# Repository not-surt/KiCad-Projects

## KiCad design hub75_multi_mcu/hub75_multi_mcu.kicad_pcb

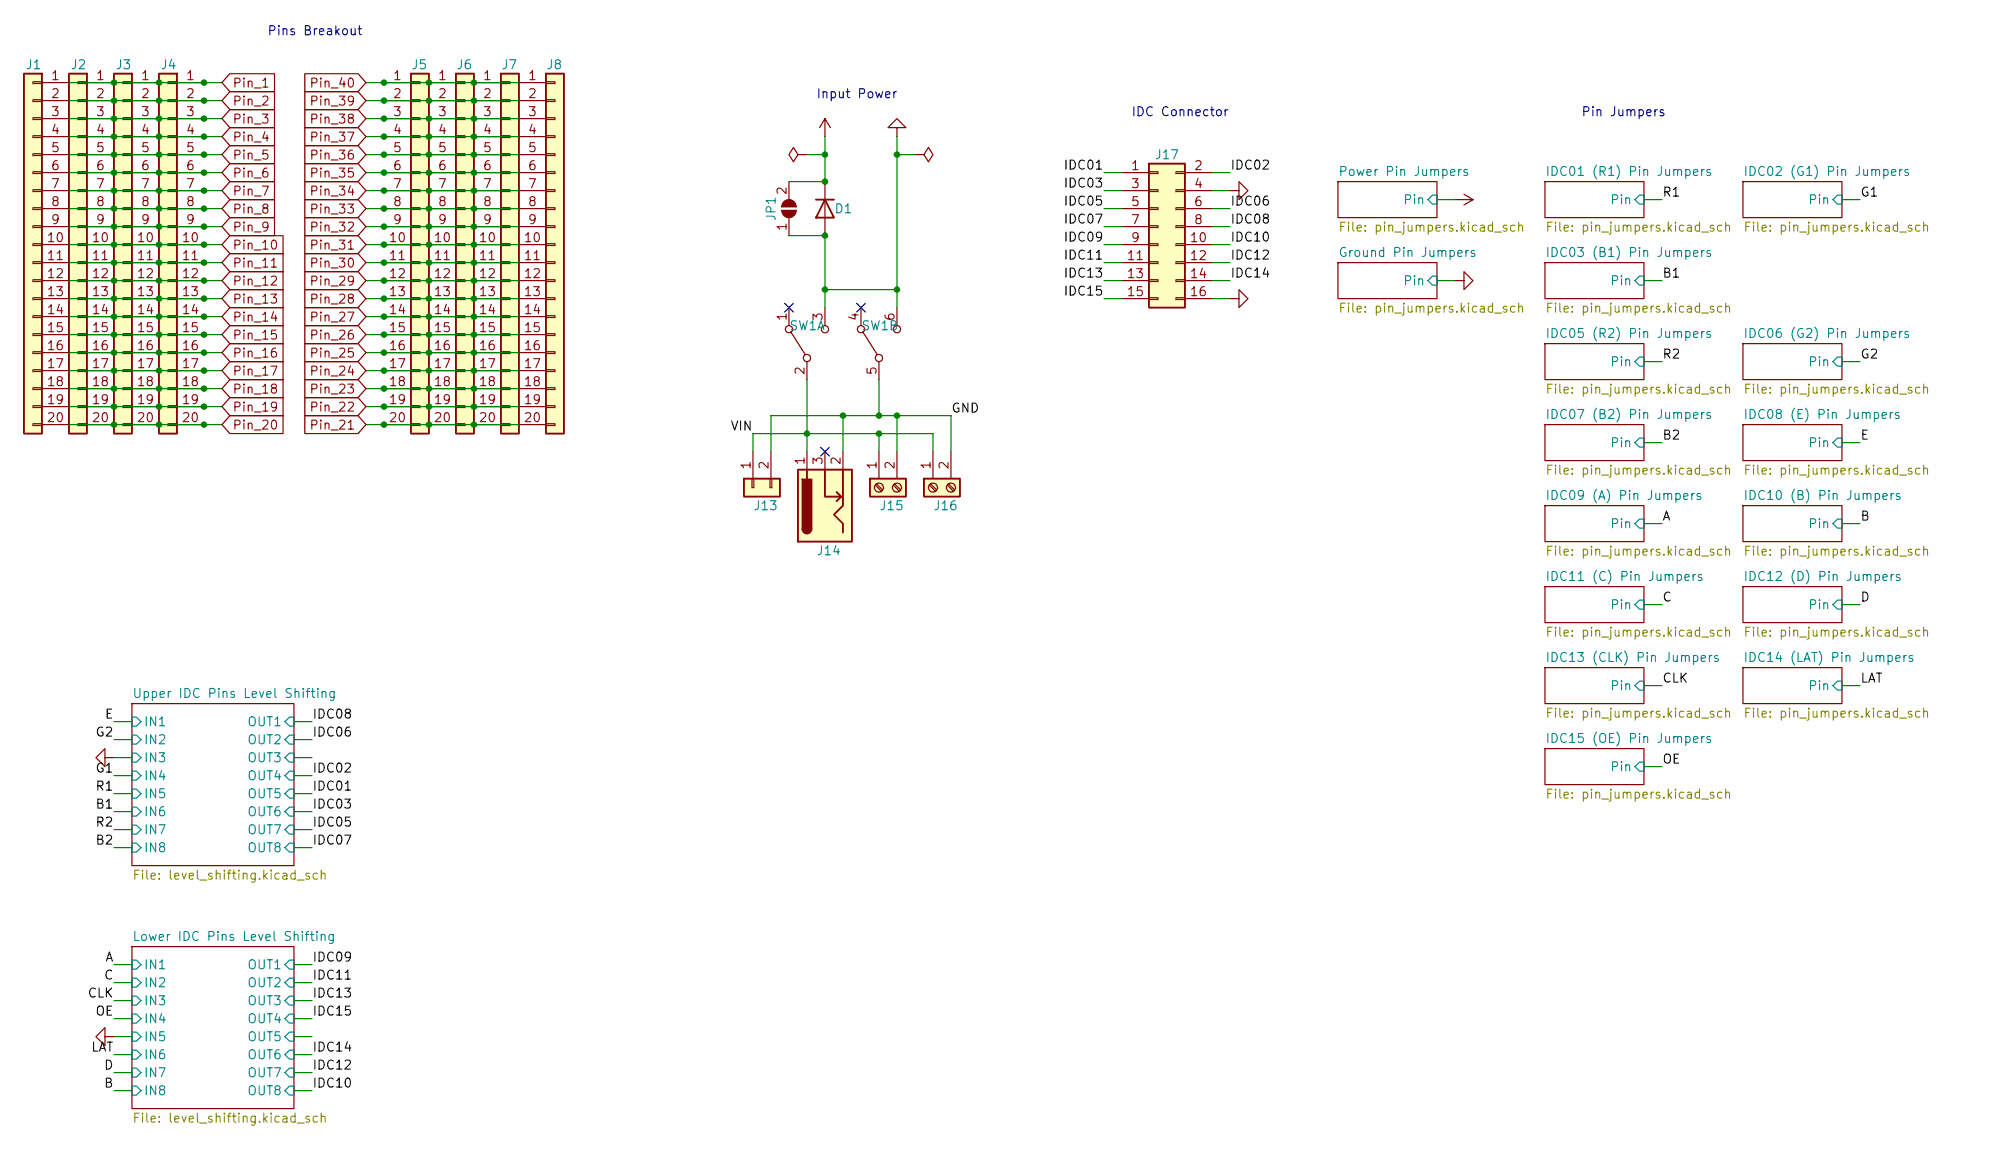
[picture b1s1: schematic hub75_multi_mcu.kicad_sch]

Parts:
D1: D; D_SMA
J1, J2, J3, J4, J5, J6, J7, J8: Conn_01x20; PinHeader_1x20_P2.54mm_Vertical_No_Silk
J13: Conn_01x02; PinHeader_1x02_P2.54mm_Vertical
J14: Barrel_Jack; BarrelJack_Horizontal
J15: Screw_Terminal_01x02; TerminalBlock_bornier-2_P5.08mm
J16: Screw_Terminal_01x02; Barrier_Block
J17: Conn_02x08_Odd_Even; IDC-Header_2x08_P2.54mm_Vertical
JP1: SolderJumper_2_Open; SolderJumper-mini-2
SW1: SW_DPDT; SW_CuK_JS202011CQN_DPDT_Straight

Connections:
/IDC01: J17.1; also elsewhere on the board
/IDC02: J17.2; also elsewhere on the board
/IDC03: J17.3; also elsewhere on the board
/IDC05: J17.5; also elsewhere on the board
/IDC06: J17.6; also elsewhere on the board
/IDC07: J17.7; also elsewhere on the board
/IDC08: J17.8; also elsewhere on the board
/IDC09: J17.9; also elsewhere on the board
/IDC10: J17.10; also elsewhere on the board
/IDC11: J17.11; also elsewhere on the board
/IDC12: J17.12; also elsewhere on the board
/IDC13: J17.13; also elsewhere on the board
/IDC14: J17.14; also elsewhere on the board
/IDC15: J17.15; also elsewhere on the board
/VIN: J13.1, J14.1, J15.1, J16.1, SW1.2 (B)
GND: D1.2 (A), J13.2, J14.2, J15.2, J16.2, J17.4, J17.16, JP1.1 (A), SW1.3 (C), SW1.5 (B), SW1.6 (C); also elsewhere on the board
Pin_1: J1.1, J2.1, J3.1, J4.1; also elsewhere on the board
Pin_2: J1.2, J2.2, J3.2, J4.2; also elsewhere on the board
Pin_3: J1.3, J2.3, J3.3, J4.3; also elsewhere on the board
Pin_4: J1.4, J2.4, J3.4, J4.4; also elsewhere on the board
Pin_5: J1.5, J2.5, J3.5, J4.5; also elsewhere on the board
Pin_6: J1.6, J2.6, J3.6, J4.6; also elsewhere on the board
Pin_7: J1.7, J2.7, J3.7, J4.7; also elsewhere on the board
Pin_8: J1.8, J2.8, J3.8, J4.8; also elsewhere on the board
Pin_9: J1.9, J2.9, J3.9, J4.9; also elsewhere on the board
Pin_10: J1.10, J2.10, J3.10, J4.10; also elsewhere on the board
Pin_11: J1.11, J2.11, J3.11, J4.11; also elsewhere on the board
Pin_12: J1.12, J2.12, J3.12, J4.12; also elsewhere on the board
Pin_13: J1.13, J2.13, J3.13, J4.13; also elsewhere on the board
Pin_14: J1.14, J2.14, J3.14, J4.14; also elsewhere on the board
Pin_15: J1.15, J2.15, J3.15, J4.15; also elsewhere on the board
Pin_16: J1.16, J2.16, J3.16, J4.16; also elsewhere on the board
Pin_17: J1.17, J2.17, J3.17, J4.17; also elsewhere on the board
Pin_18: J1.18, J2.18, J3.18, J4.18; also elsewhere on the board
Pin_19: J1.19, J2.19, J3.19, J4.19; also elsewhere on the board
Pin_20: J1.20, J2.20, J3.20, J4.20; also elsewhere on the board
Pin_21: J5.20, J6.20, J7.20, J8.20; also elsewhere on the board
Pin_22: J5.19, J6.19, J7.19, J8.19; also elsewhere on the board
Pin_23: J5.18, J6.18, J7.18, J8.18; also elsewhere on the board
Pin_24: J5.17, J6.17, J7.17, J8.17; also elsewhere on the board
Pin_25: J5.16, J6.16, J7.16, J8.16; also elsewhere on the board
Pin_26: J5.15, J6.15, J7.15, J8.15; also elsewhere on the board
Pin_27: J5.14, J6.14, J7.14, J8.14; also elsewhere on the board
Pin_28: J5.13, J6.13, J7.13, J8.13; also elsewhere on the board
Pin_29: J5.12, J6.12, J7.12, J8.12; also elsewhere on the board
Pin_30: J5.11, J6.11, J7.11, J8.11; also elsewhere on the board
Pin_31: J5.10, J6.10, J7.10, J8.10; also elsewhere on the board
Pin_32: J5.9, J6.9, J7.9, J8.9; also elsewhere on the board
Pin_33: J5.8, J6.8, J7.8, J8.8; also elsewhere on the board
Pin_34: J5.7, J6.7, J7.7, J8.7; also elsewhere on the board
Pin_35: J5.6, J6.6, J7.6, J8.6; also elsewhere on the board
Pin_36: J5.5, J6.5, J7.5, J8.5; also elsewhere on the board
Pin_37: J5.4, J6.4, J7.4, J8.4; also elsewhere on the board
Pin_38: J5.3, J6.3, J7.3, J8.3; also elsewhere on the board
Pin_39: J5.2, J6.2, J7.2, J8.2; also elsewhere on the board
Pin_40: J5.1, J6.1, J7.1, J8.1; also elsewhere on the board
VCC: D1.1 (K), JP1.2 (B); also elsewhere on the board

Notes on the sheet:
Pins Breakout
IDC Connector
Input Power
Pin Jumpers

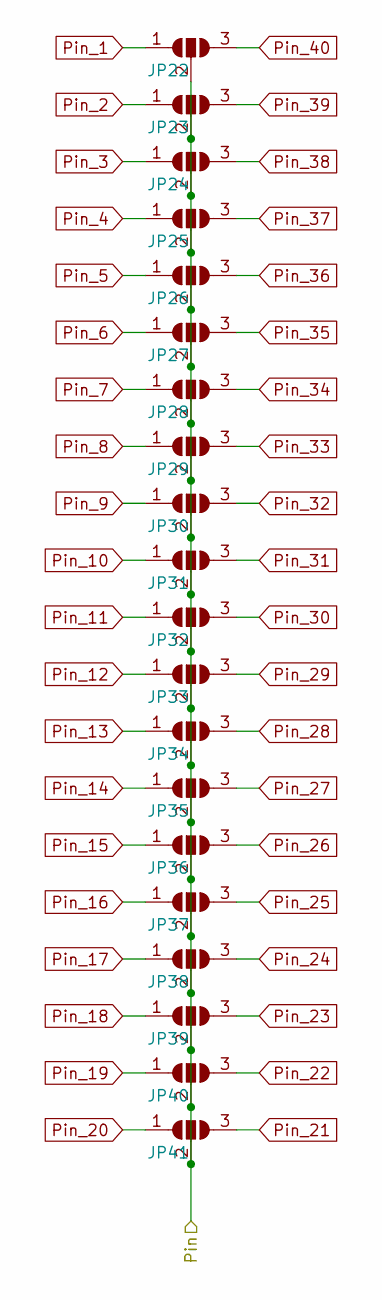
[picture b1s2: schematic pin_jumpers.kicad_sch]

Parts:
JP22, JP23, JP24, JP25, JP26, JP27, JP28, JP29, JP30, JP31, JP32, JP33, JP34, JP35, JP36, JP37, JP38, JP39, JP40, JP41: SolderJumper_3_Open; SolderJumper-mini-3

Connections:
Pin_1: JP22.1 (A); also elsewhere on the board
Pin_2: JP23.1 (A); also elsewhere on the board
Pin_3: JP24.1 (A); also elsewhere on the board
Pin_4: JP25.1 (A); also elsewhere on the board
Pin_5: JP26.1 (A); also elsewhere on the board
Pin_6: JP27.1 (A); also elsewhere on the board
Pin_7: JP28.1 (A); also elsewhere on the board
Pin_8: JP29.1 (A); also elsewhere on the board
Pin_9: JP30.1 (A); also elsewhere on the board
Pin_10: JP31.1 (A); also elsewhere on the board
Pin_11: JP32.1 (A); also elsewhere on the board
Pin_12: JP33.1 (A); also elsewhere on the board
Pin_13: JP34.1 (A); also elsewhere on the board
Pin_14: JP35.1 (A); also elsewhere on the board
Pin_15: JP36.1 (A); also elsewhere on the board
Pin_16: JP37.1 (A); also elsewhere on the board
Pin_17: JP38.1 (A); also elsewhere on the board
Pin_18: JP39.1 (A); also elsewhere on the board
Pin_19: JP40.1 (A); also elsewhere on the board
Pin_20: JP41.1 (A); also elsewhere on the board
Pin_21: JP41.3 (B); also elsewhere on the board
Pin_22: JP40.3 (B); also elsewhere on the board
Pin_23: JP39.3 (B); also elsewhere on the board
Pin_24: JP38.3 (B); also elsewhere on the board
Pin_25: JP37.3 (B); also elsewhere on the board
Pin_26: JP36.3 (B); also elsewhere on the board
Pin_27: JP35.3 (B); also elsewhere on the board
Pin_28: JP34.3 (B); also elsewhere on the board
Pin_29: JP33.3 (B); also elsewhere on the board
Pin_30: JP32.3 (B); also elsewhere on the board
Pin_31: JP31.3 (B); also elsewhere on the board
Pin_32: JP30.3 (B); also elsewhere on the board
Pin_33: JP29.3 (B); also elsewhere on the board
Pin_34: JP28.3 (B); also elsewhere on the board
Pin_35: JP27.3 (B); also elsewhere on the board
Pin_36: JP26.3 (B); also elsewhere on the board
Pin_37: JP25.3 (B); also elsewhere on the board
Pin_38: JP24.3 (B); also elsewhere on the board
Pin_39: JP23.3 (B); also elsewhere on the board
Pin_40: JP22.3 (B); also elsewhere on the board
VCC: JP22.2 (C), JP23.2 (C), JP24.2 (C), JP25.2 (C), JP26.2 (C), JP27.2 (C), JP28.2 (C), JP29.2 (C), JP30.2 (C), JP31.2 (C), JP32.2 (C), JP33.2 (C), JP34.2 (C), JP35.2 (C), JP36.2 (C), JP37.2 (C), JP38.2 (C), JP39.2 (C), JP40.2 (C), JP41.2 (C); also elsewhere on the board

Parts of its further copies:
JP2, JP3, JP4, JP5, JP6, JP7, JP8, JP9, JP10, JP11, JP12, JP13, JP14, JP15, JP16, JP17, JP18, JP19, JP20, JP21, JP42, JP43, JP44, JP45, JP46, JP47, JP48, JP49, JP50, JP51, JP52, JP53, JP54, JP55, JP56, JP57, JP58, JP59, JP60, JP61, JP62, JP63, JP64, JP65, JP66, JP67, JP68, JP69, JP70, JP71, JP72, JP73, JP74, JP75, JP76, JP77, JP78, JP79, JP80, JP81, JP82, JP83, JP84, JP85, JP86, JP87, JP88, JP89, JP90, JP91, JP92, JP93, JP94, JP95, JP96, JP97, JP98, JP99, JP100, JP101, JP102, JP103, JP104, JP105, JP106, JP107, JP108, JP109, JP110, JP111, JP112, JP113, JP114, JP115, JP116, JP117, JP118, JP119, JP120, JP121, JP122, JP123, JP124, JP125, JP126, JP127, JP128, JP129, JP130, JP131, JP132, JP133, JP134, JP135, JP136, JP137, JP138, JP139, JP140, JP141, JP142, JP143, JP144, JP145, JP146, JP147, JP148, JP149, JP150, JP151, JP152, JP153, JP154, JP155, JP156, JP157, JP158, JP159, JP160, JP161, JP162, JP163, JP164, JP165, JP166, JP167, JP168, JP169, JP170, JP171, JP172, JP173, JP174, JP175, JP176, JP177, JP178, JP179, JP180, JP181, JP182, JP183, JP184, JP185, JP186, JP187, JP188, JP189, JP190, JP191, JP192, JP193, JP194, JP195, JP196, JP197, JP198, JP199, JP200, JP201, JP202, JP203, JP204, JP205, JP206, JP207, JP208, JP209, JP210, JP211, JP212, JP213, JP214, JP215, JP216, JP217, JP218, JP219, JP220, JP221, JP222, JP223, JP224, JP225, JP226, JP227, JP228, JP229, JP230, JP231, JP232, JP233, JP234, JP235, JP236, JP237, JP238, JP239, JP240, JP241, JP242, JP243, JP244, JP245, JP246, JP247, JP248, JP249, JP250, JP251, JP252, JP253, JP254, JP255, JP256, JP257, JP258, JP259, JP260, JP261, JP262, JP263, JP264, JP265, JP266, JP267, JP268, JP269, JP270, JP271, JP272, JP273, JP274, JP275, JP276, JP277, JP278, JP279, JP280, JP281, JP282, JP283, JP284, JP285, JP286, JP287, JP288, JP289, JP290, JP291, JP292, JP293, JP294, JP295, JP296, JP297, JP298, JP299, JP300, JP301, JP302, JP303, JP304, JP305, JP306, JP307, JP308, JP309, JP310, JP311, JP312, JP313, JP314, JP315, JP316, JP317, JP318, JP319, JP320, JP321: SolderJumper_3_Open; SolderJumper-mini-3

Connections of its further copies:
/A: JP182.2 (C), JP183.2 (C), JP184.2 (C), JP185.2 (C), JP186.2 (C), JP187.2 (C), JP188.2 (C), JP189.2 (C), JP190.2 (C), JP191.2 (C), JP192.2 (C), JP193.2 (C), JP194.2 (C), JP195.2 (C), JP196.2 (C), JP197.2 (C), JP198.2 (C), JP199.2 (C), JP200.2 (C), JP201.2 (C); also elsewhere on the board
/B: JP202.2 (C), JP203.2 (C), JP204.2 (C), JP205.2 (C), JP206.2 (C), JP207.2 (C), JP208.2 (C), JP209.2 (C), JP210.2 (C), JP211.2 (C), JP212.2 (C), JP213.2 (C), JP214.2 (C), JP215.2 (C), JP216.2 (C), JP217.2 (C), JP218.2 (C), JP219.2 (C), JP220.2 (C), JP221.2 (C); also elsewhere on the board
/B1: JP82.2 (C), JP83.2 (C), JP84.2 (C), JP85.2 (C), JP86.2 (C), JP87.2 (C), JP88.2 (C), JP89.2 (C), JP90.2 (C), JP91.2 (C), JP92.2 (C), JP93.2 (C), JP94.2 (C), JP95.2 (C), JP96.2 (C), JP97.2 (C), JP98.2 (C), JP99.2 (C), JP100.2 (C), JP101.2 (C); also elsewhere on the board
/B2: JP142.2 (C), JP143.2 (C), JP144.2 (C), JP145.2 (C), JP146.2 (C), JP147.2 (C), JP148.2 (C), JP149.2 (C), JP150.2 (C), JP151.2 (C), JP152.2 (C), JP153.2 (C), JP154.2 (C), JP155.2 (C), JP156.2 (C), JP157.2 (C), JP158.2 (C), JP159.2 (C), JP160.2 (C), JP161.2 (C); also elsewhere on the board
/C: JP222.2 (C), JP223.2 (C), JP224.2 (C), JP225.2 (C), JP226.2 (C), JP227.2 (C), JP228.2 (C), JP229.2 (C), JP230.2 (C), JP231.2 (C), JP232.2 (C), JP233.2 (C), JP234.2 (C), JP235.2 (C), JP236.2 (C), JP237.2 (C), JP238.2 (C), JP239.2 (C), JP240.2 (C), JP241.2 (C); also elsewhere on the board
/CLK: JP262.2 (C), JP263.2 (C), JP264.2 (C), JP265.2 (C), JP266.2 (C), JP267.2 (C), JP268.2 (C), JP269.2 (C), JP270.2 (C), JP271.2 (C), JP272.2 (C), JP273.2 (C), JP274.2 (C), JP275.2 (C), JP276.2 (C), JP277.2 (C), JP278.2 (C), JP279.2 (C), JP280.2 (C), JP281.2 (C); also elsewhere on the board
/D: JP242.2 (C), JP243.2 (C), JP244.2 (C), JP245.2 (C), JP246.2 (C), JP247.2 (C), JP248.2 (C), JP249.2 (C), JP250.2 (C), JP251.2 (C), JP252.2 (C), JP253.2 (C), JP254.2 (C), JP255.2 (C), JP256.2 (C), JP257.2 (C), JP258.2 (C), JP259.2 (C), JP260.2 (C), JP261.2 (C); also elsewhere on the board
/E: JP162.2 (C), JP163.2 (C), JP164.2 (C), JP165.2 (C), JP166.2 (C), JP167.2 (C), JP168.2 (C), JP169.2 (C), JP170.2 (C), JP171.2 (C), JP172.2 (C), JP173.2 (C), JP174.2 (C), JP175.2 (C), JP176.2 (C), JP177.2 (C), JP178.2 (C), JP179.2 (C), JP180.2 (C), JP181.2 (C); also elsewhere on the board
/G1: JP62.2 (C), JP63.2 (C), JP64.2 (C), JP65.2 (C), JP66.2 (C), JP67.2 (C), JP68.2 (C), JP69.2 (C), JP70.2 (C), JP71.2 (C), JP72.2 (C), JP73.2 (C), JP74.2 (C), JP75.2 (C), JP76.2 (C), JP77.2 (C), JP78.2 (C), JP79.2 (C), JP80.2 (C), JP81.2 (C); also elsewhere on the board
/G2: JP122.2 (C), JP123.2 (C), JP124.2 (C), JP125.2 (C), JP126.2 (C), JP127.2 (C), JP128.2 (C), JP129.2 (C), JP130.2 (C), JP131.2 (C), JP132.2 (C), JP133.2 (C), JP134.2 (C), JP135.2 (C), JP136.2 (C), JP137.2 (C), JP138.2 (C), JP139.2 (C), JP140.2 (C), JP141.2 (C); also elsewhere on the board
/LAT: JP282.2 (C), JP283.2 (C), JP284.2 (C), JP285.2 (C), JP286.2 (C), JP287.2 (C), JP288.2 (C), JP289.2 (C), JP290.2 (C), JP291.2 (C), JP292.2 (C), JP293.2 (C), JP294.2 (C), JP295.2 (C), JP296.2 (C), JP297.2 (C), JP298.2 (C), JP299.2 (C), JP300.2 (C), JP301.2 (C); also elsewhere on the board
/OE: JP302.2 (C), JP303.2 (C), JP304.2 (C), JP305.2 (C), JP306.2 (C), JP307.2 (C), JP308.2 (C), JP309.2 (C), JP310.2 (C), JP311.2 (C), JP312.2 (C), JP313.2 (C), JP314.2 (C), JP315.2 (C), JP316.2 (C), JP317.2 (C), JP318.2 (C), JP319.2 (C), JP320.2 (C), JP321.2 (C); also elsewhere on the board
/R1: JP42.2 (C), JP43.2 (C), JP44.2 (C), JP45.2 (C), JP46.2 (C), JP47.2 (C), JP48.2 (C), JP49.2 (C), JP50.2 (C), JP51.2 (C), JP52.2 (C), JP53.2 (C), JP54.2 (C), JP55.2 (C), JP56.2 (C), JP57.2 (C), JP58.2 (C), JP59.2 (C), JP60.2 (C), JP61.2 (C); also elsewhere on the board
/R2: JP102.2 (C), JP103.2 (C), JP104.2 (C), JP105.2 (C), JP106.2 (C), JP107.2 (C), JP108.2 (C), JP109.2 (C), JP110.2 (C), JP111.2 (C), JP112.2 (C), JP113.2 (C), JP114.2 (C), JP115.2 (C), JP116.2 (C), JP117.2 (C), JP118.2 (C), JP119.2 (C), JP120.2 (C), JP121.2 (C); also elsewhere on the board
GND: JP2.2 (C), JP3.2 (C), JP4.2 (C), JP5.2 (C), JP6.2 (C), JP7.2 (C), JP8.2 (C), JP9.2 (C), JP10.2 (C), JP11.2 (C), JP12.2 (C), JP13.2 (C), JP14.2 (C), JP15.2 (C), JP16.2 (C), JP17.2 (C), JP18.2 (C), JP19.2 (C), JP20.2 (C), JP21.2 (C); also elsewhere on the board
Pin_1: JP2.1 (A), JP42.1 (A), JP62.1 (A), JP82.1 (A), JP102.1 (A), JP122.1 (A), JP142.1 (A), JP162.1 (A), JP182.1 (A), JP202.1 (A), JP222.1 (A), JP242.1 (A), JP262.1 (A), JP282.1 (A), JP302.1 (A); also elsewhere on the board
Pin_2: JP3.1 (A), JP43.1 (A), JP63.1 (A), JP83.1 (A), JP103.1 (A), JP123.1 (A), JP143.1 (A), JP163.1 (A), JP183.1 (A), JP203.1 (A), JP223.1 (A), JP243.1 (A), JP263.1 (A), JP283.1 (A), JP303.1 (A); also elsewhere on the board
Pin_3: JP4.1 (A), JP44.1 (A), JP64.1 (A), JP84.1 (A), JP104.1 (A), JP124.1 (A), JP144.1 (A), JP164.1 (A), JP184.1 (A), JP204.1 (A), JP224.1 (A), JP244.1 (A), JP264.1 (A), JP284.1 (A), JP304.1 (A); also elsewhere on the board
Pin_4: JP5.1 (A), JP45.1 (A), JP65.1 (A), JP85.1 (A), JP105.1 (A), JP125.1 (A), JP145.1 (A), JP165.1 (A), JP185.1 (A), JP205.1 (A), JP225.1 (A), JP245.1 (A), JP265.1 (A), JP285.1 (A), JP305.1 (A); also elsewhere on the board
Pin_5: JP6.1 (A), JP46.1 (A), JP66.1 (A), JP86.1 (A), JP106.1 (A), JP126.1 (A), JP146.1 (A), JP166.1 (A), JP186.1 (A), JP206.1 (A), JP226.1 (A), JP246.1 (A), JP266.1 (A), JP286.1 (A), JP306.1 (A); also elsewhere on the board
Pin_6: JP7.1 (A), JP47.1 (A), JP67.1 (A), JP87.1 (A), JP107.1 (A), JP127.1 (A), JP147.1 (A), JP167.1 (A), JP187.1 (A), JP207.1 (A), JP227.1 (A), JP247.1 (A), JP267.1 (A), JP287.1 (A), JP307.1 (A); also elsewhere on the board
Pin_7: JP8.1 (A), JP48.1 (A), JP68.1 (A), JP88.1 (A), JP108.1 (A), JP128.1 (A), JP148.1 (A), JP168.1 (A), JP188.1 (A), JP208.1 (A), JP228.1 (A), JP248.1 (A), JP268.1 (A), JP288.1 (A), JP308.1 (A); also elsewhere on the board
Pin_8: JP9.1 (A), JP49.1 (A), JP69.1 (A), JP89.1 (A), JP109.1 (A), JP129.1 (A), JP149.1 (A), JP169.1 (A), JP189.1 (A), JP209.1 (A), JP229.1 (A), JP249.1 (A), JP269.1 (A), JP289.1 (A), JP309.1 (A); also elsewhere on the board
Pin_9: JP10.1 (A), JP50.1 (A), JP70.1 (A), JP90.1 (A), JP110.1 (A), JP130.1 (A), JP150.1 (A), JP170.1 (A), JP190.1 (A), JP210.1 (A), JP230.1 (A), JP250.1 (A), JP270.1 (A), JP290.1 (A), JP310.1 (A); also elsewhere on the board
Pin_10: JP11.1 (A), JP51.1 (A), JP71.1 (A), JP91.1 (A), JP111.1 (A), JP131.1 (A), JP151.1 (A), JP171.1 (A), JP191.1 (A), JP211.1 (A), JP231.1 (A), JP251.1 (A), JP271.1 (A), JP291.1 (A), JP311.1 (A); also elsewhere on the board
Pin_11: JP12.1 (A), JP52.1 (A), JP72.1 (A), JP92.1 (A), JP112.1 (A), JP132.1 (A), JP152.1 (A), JP172.1 (A), JP192.1 (A), JP212.1 (A), JP232.1 (A), JP252.1 (A), JP272.1 (A), JP292.1 (A), JP312.1 (A); also elsewhere on the board
Pin_12: JP13.1 (A), JP53.1 (A), JP73.1 (A), JP93.1 (A), JP113.1 (A), JP133.1 (A), JP153.1 (A), JP173.1 (A), JP193.1 (A), JP213.1 (A), JP233.1 (A), JP253.1 (A), JP273.1 (A), JP293.1 (A), JP313.1 (A); also elsewhere on the board
Pin_13: JP14.1 (A), JP54.1 (A), JP74.1 (A), JP94.1 (A), JP114.1 (A), JP134.1 (A), JP154.1 (A), JP174.1 (A), JP194.1 (A), JP214.1 (A), JP234.1 (A), JP254.1 (A), JP274.1 (A), JP294.1 (A), JP314.1 (A); also elsewhere on the board
Pin_14: JP15.1 (A), JP55.1 (A), JP75.1 (A), JP95.1 (A), JP115.1 (A), JP135.1 (A), JP155.1 (A), JP175.1 (A), JP195.1 (A), JP215.1 (A), JP235.1 (A), JP255.1 (A), JP275.1 (A), JP295.1 (A), JP315.1 (A); also elsewhere on the board
Pin_15: JP16.1 (A), JP56.1 (A), JP76.1 (A), JP96.1 (A), JP116.1 (A), JP136.1 (A), JP156.1 (A), JP176.1 (A), JP196.1 (A), JP216.1 (A), JP236.1 (A), JP256.1 (A), JP276.1 (A), JP296.1 (A), JP316.1 (A); also elsewhere on the board
Pin_16: JP17.1 (A), JP57.1 (A), JP77.1 (A), JP97.1 (A), JP117.1 (A), JP137.1 (A), JP157.1 (A), JP177.1 (A), JP197.1 (A), JP217.1 (A), JP237.1 (A), JP257.1 (A), JP277.1 (A), JP297.1 (A), JP317.1 (A); also elsewhere on the board
Pin_17: JP18.1 (A), JP58.1 (A), JP78.1 (A), JP98.1 (A), JP118.1 (A), JP138.1 (A), JP158.1 (A), JP178.1 (A), JP198.1 (A), JP218.1 (A), JP238.1 (A), JP258.1 (A), JP278.1 (A), JP298.1 (A), JP318.1 (A); also elsewhere on the board
Pin_18: JP19.1 (A), JP59.1 (A), JP79.1 (A), JP99.1 (A), JP119.1 (A), JP139.1 (A), JP159.1 (A), JP179.1 (A), JP199.1 (A), JP219.1 (A), JP239.1 (A), JP259.1 (A), JP279.1 (A), JP299.1 (A), JP319.1 (A); also elsewhere on the board
Pin_19: JP20.1 (A), JP60.1 (A), JP80.1 (A), JP100.1 (A), JP120.1 (A), JP140.1 (A), JP160.1 (A), JP180.1 (A), JP200.1 (A), JP220.1 (A), JP240.1 (A), JP260.1 (A), JP280.1 (A), JP300.1 (A), JP320.1 (A); also elsewhere on the board
Pin_20: JP21.1 (A), JP61.1 (A), JP81.1 (A), JP101.1 (A), JP121.1 (A), JP141.1 (A), JP161.1 (A), JP181.1 (A), JP201.1 (A), JP221.1 (A), JP241.1 (A), JP261.1 (A), JP281.1 (A), JP301.1 (A), JP321.1 (A); also elsewhere on the board
Pin_21: JP21.3 (B), JP61.3 (B), JP81.3 (B), JP101.3 (B), JP121.3 (B), JP141.3 (B), JP161.3 (B), JP181.3 (B), JP201.3 (B), JP221.3 (B), JP241.3 (B), JP261.3 (B), JP281.3 (B), JP301.3 (B), JP321.3 (B); also elsewhere on the board
Pin_22: JP20.3 (B), JP60.3 (B), JP80.3 (B), JP100.3 (B), JP120.3 (B), JP140.3 (B), JP160.3 (B), JP180.3 (B), JP200.3 (B), JP220.3 (B), JP240.3 (B), JP260.3 (B), JP280.3 (B), JP300.3 (B), JP320.3 (B); also elsewhere on the board
Pin_23: JP19.3 (B), JP59.3 (B), JP79.3 (B), JP99.3 (B), JP119.3 (B), JP139.3 (B), JP159.3 (B), JP179.3 (B), JP199.3 (B), JP219.3 (B), JP239.3 (B), JP259.3 (B), JP279.3 (B), JP299.3 (B), JP319.3 (B); also elsewhere on the board
Pin_24: JP18.3 (B), JP58.3 (B), JP78.3 (B), JP98.3 (B), JP118.3 (B), JP138.3 (B), JP158.3 (B), JP178.3 (B), JP198.3 (B), JP218.3 (B), JP238.3 (B), JP258.3 (B), JP278.3 (B), JP298.3 (B), JP318.3 (B); also elsewhere on the board
Pin_25: JP17.3 (B), JP57.3 (B), JP77.3 (B), JP97.3 (B), JP117.3 (B), JP137.3 (B), JP157.3 (B), JP177.3 (B), JP197.3 (B), JP217.3 (B), JP237.3 (B), JP257.3 (B), JP277.3 (B), JP297.3 (B), JP317.3 (B); also elsewhere on the board
Pin_26: JP16.3 (B), JP56.3 (B), JP76.3 (B), JP96.3 (B), JP116.3 (B), JP136.3 (B), JP156.3 (B), JP176.3 (B), JP196.3 (B), JP216.3 (B), JP236.3 (B), JP256.3 (B), JP276.3 (B), JP296.3 (B), JP316.3 (B); also elsewhere on the board
Pin_27: JP15.3 (B), JP55.3 (B), JP75.3 (B), JP95.3 (B), JP115.3 (B), JP135.3 (B), JP155.3 (B), JP175.3 (B), JP195.3 (B), JP215.3 (B), JP235.3 (B), JP255.3 (B), JP275.3 (B), JP295.3 (B), JP315.3 (B); also elsewhere on the board
Pin_28: JP14.3 (B), JP54.3 (B), JP74.3 (B), JP94.3 (B), JP114.3 (B), JP134.3 (B), JP154.3 (B), JP174.3 (B), JP194.3 (B), JP214.3 (B), JP234.3 (B), JP254.3 (B), JP274.3 (B), JP294.3 (B), JP314.3 (B); also elsewhere on the board
Pin_29: JP13.3 (B), JP53.3 (B), JP73.3 (B), JP93.3 (B), JP113.3 (B), JP133.3 (B), JP153.3 (B), JP173.3 (B), JP193.3 (B), JP213.3 (B), JP233.3 (B), JP253.3 (B), JP273.3 (B), JP293.3 (B), JP313.3 (B); also elsewhere on the board
Pin_30: JP12.3 (B), JP52.3 (B), JP72.3 (B), JP92.3 (B), JP112.3 (B), JP132.3 (B), JP152.3 (B), JP172.3 (B), JP192.3 (B), JP212.3 (B), JP232.3 (B), JP252.3 (B), JP272.3 (B), JP292.3 (B), JP312.3 (B); also elsewhere on the board
Pin_31: JP11.3 (B), JP51.3 (B), JP71.3 (B), JP91.3 (B), JP111.3 (B), JP131.3 (B), JP151.3 (B), JP171.3 (B), JP191.3 (B), JP211.3 (B), JP231.3 (B), JP251.3 (B), JP271.3 (B), JP291.3 (B), JP311.3 (B); also elsewhere on the board
Pin_32: JP10.3 (B), JP50.3 (B), JP70.3 (B), JP90.3 (B), JP110.3 (B), JP130.3 (B), JP150.3 (B), JP170.3 (B), JP190.3 (B), JP210.3 (B), JP230.3 (B), JP250.3 (B), JP270.3 (B), JP290.3 (B), JP310.3 (B); also elsewhere on the board
Pin_33: JP9.3 (B), JP49.3 (B), JP69.3 (B), JP89.3 (B), JP109.3 (B), JP129.3 (B), JP149.3 (B), JP169.3 (B), JP189.3 (B), JP209.3 (B), JP229.3 (B), JP249.3 (B), JP269.3 (B), JP289.3 (B), JP309.3 (B); also elsewhere on the board
Pin_34: JP8.3 (B), JP48.3 (B), JP68.3 (B), JP88.3 (B), JP108.3 (B), JP128.3 (B), JP148.3 (B), JP168.3 (B), JP188.3 (B), JP208.3 (B), JP228.3 (B), JP248.3 (B), JP268.3 (B), JP288.3 (B), JP308.3 (B); also elsewhere on the board
Pin_35: JP7.3 (B), JP47.3 (B), JP67.3 (B), JP87.3 (B), JP107.3 (B), JP127.3 (B), JP147.3 (B), JP167.3 (B), JP187.3 (B), JP207.3 (B), JP227.3 (B), JP247.3 (B), JP267.3 (B), JP287.3 (B), JP307.3 (B); also elsewhere on the board
Pin_36: JP6.3 (B), JP46.3 (B), JP66.3 (B), JP86.3 (B), JP106.3 (B), JP126.3 (B), JP146.3 (B), JP166.3 (B), JP186.3 (B), JP206.3 (B), JP226.3 (B), JP246.3 (B), JP266.3 (B), JP286.3 (B), JP306.3 (B); also elsewhere on the board
Pin_37: JP5.3 (B), JP45.3 (B), JP65.3 (B), JP85.3 (B), JP105.3 (B), JP125.3 (B), JP145.3 (B), JP165.3 (B), JP185.3 (B), JP205.3 (B), JP225.3 (B), JP245.3 (B), JP265.3 (B), JP285.3 (B), JP305.3 (B); also elsewhere on the board
Pin_38: JP4.3 (B), JP44.3 (B), JP64.3 (B), JP84.3 (B), JP104.3 (B), JP124.3 (B), JP144.3 (B), JP164.3 (B), JP184.3 (B), JP204.3 (B), JP224.3 (B), JP244.3 (B), JP264.3 (B), JP284.3 (B), JP304.3 (B); also elsewhere on the board
Pin_39: JP3.3 (B), JP43.3 (B), JP63.3 (B), JP83.3 (B), JP103.3 (B), JP123.3 (B), JP143.3 (B), JP163.3 (B), JP183.3 (B), JP203.3 (B), JP223.3 (B), JP243.3 (B), JP263.3 (B), JP283.3 (B), JP303.3 (B); also elsewhere on the board
Pin_40: JP2.3 (B), JP42.3 (B), JP62.3 (B), JP82.3 (B), JP102.3 (B), JP122.3 (B), JP142.3 (B), JP162.3 (B), JP182.3 (B), JP202.3 (B), JP222.3 (B), JP242.3 (B), JP262.3 (B), JP282.3 (B), JP302.3 (B); also elsewhere on the board

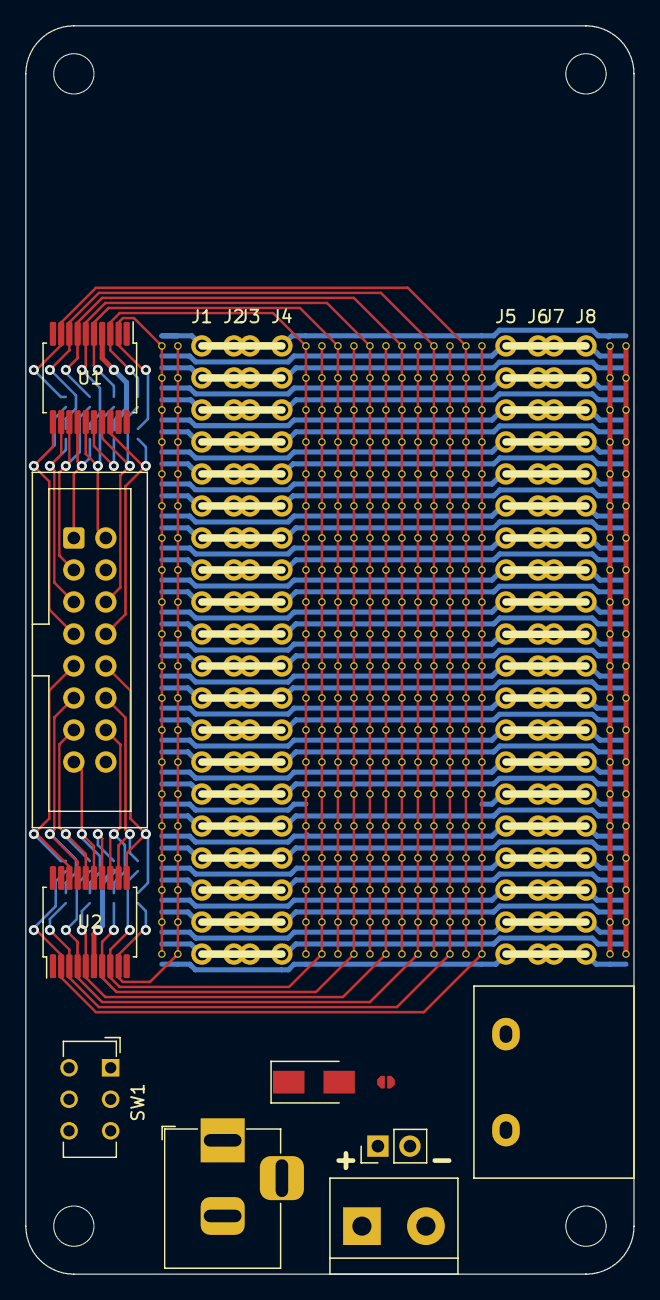
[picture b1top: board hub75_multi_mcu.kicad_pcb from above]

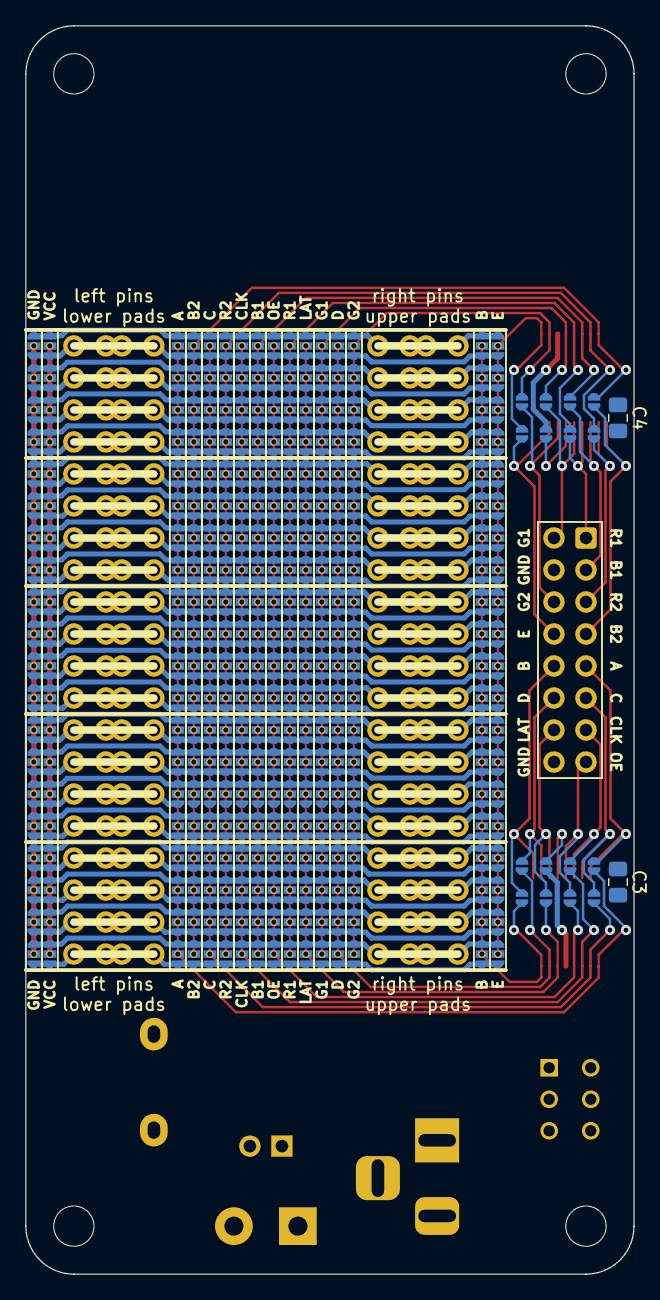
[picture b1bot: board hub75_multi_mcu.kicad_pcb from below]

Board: 2 copper layers, 48.3 x 99.1 mm, 356 parts (338 on the bottom side), 73 nets.

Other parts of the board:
C3, C4: 0.1uF; C_0805_2012Metric_Pad1.18x1.45mm_HandSolder
JP322, JP323, JP324, JP325, JP326, JP327, JP328, JP329, JP330, JP331, JP332, JP333, JP334, JP335, JP336, JP337: SolderJumper_2_Open; SolderJumper-mini-2
U1, U2: 74AHCT245; SSOP-20_5.3x7.2mm_P0.65mm

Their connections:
/A: JP330.1 (A), U2.2 (A0); also elsewhere on the board
/B: JP337.1 (A), U2.9 (A7); also elsewhere on the board
/B1: JP327.1 (A), U1.7 (A5); also elsewhere on the board
/B2: JP329.1 (A), U1.9 (A7); also elsewhere on the board
/C: JP331.1 (A), U2.3 (A1); also elsewhere on the board
/CLK: JP332.1 (A), U2.4 (A2); also elsewhere on the board
/D: JP336.1 (A), U2.8 (A6); also elsewhere on the board
/E: JP322.1 (A), U1.2 (A0); also elsewhere on the board
/G1: JP325.1 (A), U1.5 (A3); also elsewhere on the board
/G2: JP323.1 (A), U1.3 (A1); also elsewhere on the board
/IDC01: JP326.2 (B), U1.14 (B4); also elsewhere on the board
/IDC02: JP325.2 (B), U1.15 (B3); also elsewhere on the board
/IDC03: JP327.2 (B), U1.13 (B5); also elsewhere on the board
/IDC05: JP328.2 (B), U1.12 (B6); also elsewhere on the board
/IDC06: JP323.2 (B), U1.17 (B1); also elsewhere on the board
/IDC07: JP329.2 (B), U1.11 (B7); also elsewhere on the board
/IDC08: JP322.2 (B), U1.18 (B0); also elsewhere on the board
/IDC09: JP330.2 (B), U2.18 (B0); also elsewhere on the board
/IDC10: JP337.2 (B), U2.11 (B7); also elsewhere on the board
/IDC11: JP331.2 (B), U2.17 (B1); also elsewhere on the board
/IDC12: JP336.2 (B), U2.12 (B6); also elsewhere on the board
/IDC13: JP332.2 (B), U2.16 (B2); also elsewhere on the board
/IDC14: JP335.2 (B), U2.13 (B5); also elsewhere on the board
/IDC15: JP333.2 (B), U2.15 (B3); also elsewhere on the board
/LAT: JP335.1 (A), U2.7 (A5); also elsewhere on the board
/Lower IDC Pins Level Shifting/OUT5: JP334.2 (B), U2.14 (B4)
/OE: JP333.1 (A), U2.5 (A3); also elsewhere on the board
/R1: JP326.1 (A), U1.6 (A4); also elsewhere on the board
/R2: JP328.1 (A), U1.8 (A6); also elsewhere on the board
/Upper IDC Pins Level Shifting/OUT3: JP324.2 (B), U1.16 (B2)
GND: C3.2, C4.2, JP324.1 (A), JP334.1 (A), U1.4 (A2), U1.10 (GND), U1.19 (CE), U2.6 (A4), U2.10 (GND), U2.19 (CE); also elsewhere on the board
VCC: C3.1, C4.1, U1.1 (A->B), U1.20 (VCC), U2.1 (A->B), U2.20 (VCC); also elsewhere on the board

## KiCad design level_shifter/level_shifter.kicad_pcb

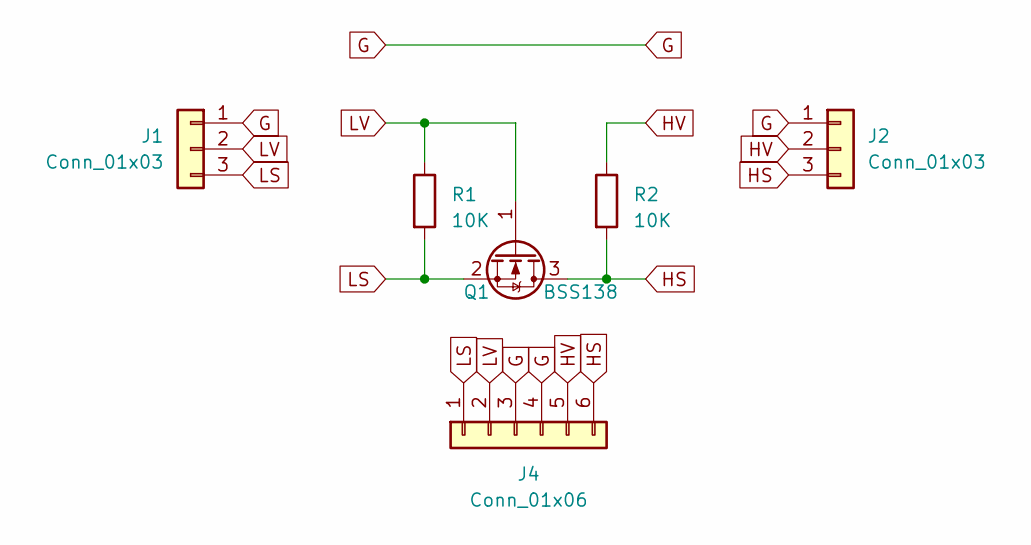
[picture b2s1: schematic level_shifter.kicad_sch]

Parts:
J1, J2: Conn_01x03; PinHeader_1x03_P2.54mm_Vertical_no_silk
J4: Conn_01x06; PinHeader_1x06_P2.54mm_Vertical_no_silk
Q1: BSS138; SOT-23_Handsoldering
R1, R2: 10K; R_0805_2012Metric_Pad1.20x1.40mm_HandSolder

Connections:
G: J1.1, J2.1, J4.3, J4.4
HS: J2.3, J4.6, Q1.3 (D), R2.2
HV: J2.2, J4.5, R2.1
LS: J1.3, J4.1, Q1.2 (S), R1.2
LV: J1.2, J4.2, Q1.1 (G), R1.1

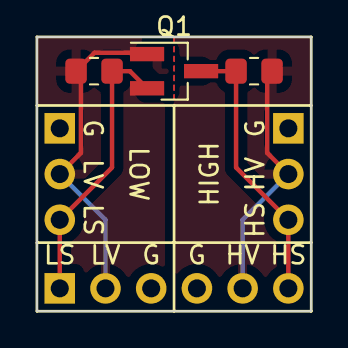
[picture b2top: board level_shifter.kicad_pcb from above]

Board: 2 copper layers, 15.2 x 15.2 mm, 6 parts (0 on the bottom side), 5 nets.

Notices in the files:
multi_expansion_board2/multi_expansion_board2.kicad_pcb:
CC0
